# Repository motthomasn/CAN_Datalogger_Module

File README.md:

# CAN_Datalogger_Module

Teensy 3.2 based CAN-Bus datalogger designed to recieve data via CAN-Bus and write the raw CAN data to a MicroSD card in binary format. A DBC file and Python script is then used to convert the binary file into CSV format for analysis.

This module was built for my CBR250RRi project but could be configured to work with any CAN-Bus data stream.

For further details on the CBR250RRi project, refer to the website https://www.cbr250rri.com/.

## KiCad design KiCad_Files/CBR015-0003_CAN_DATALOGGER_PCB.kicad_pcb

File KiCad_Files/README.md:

This folder contains the KiCad files for the CAN Datalogger Module

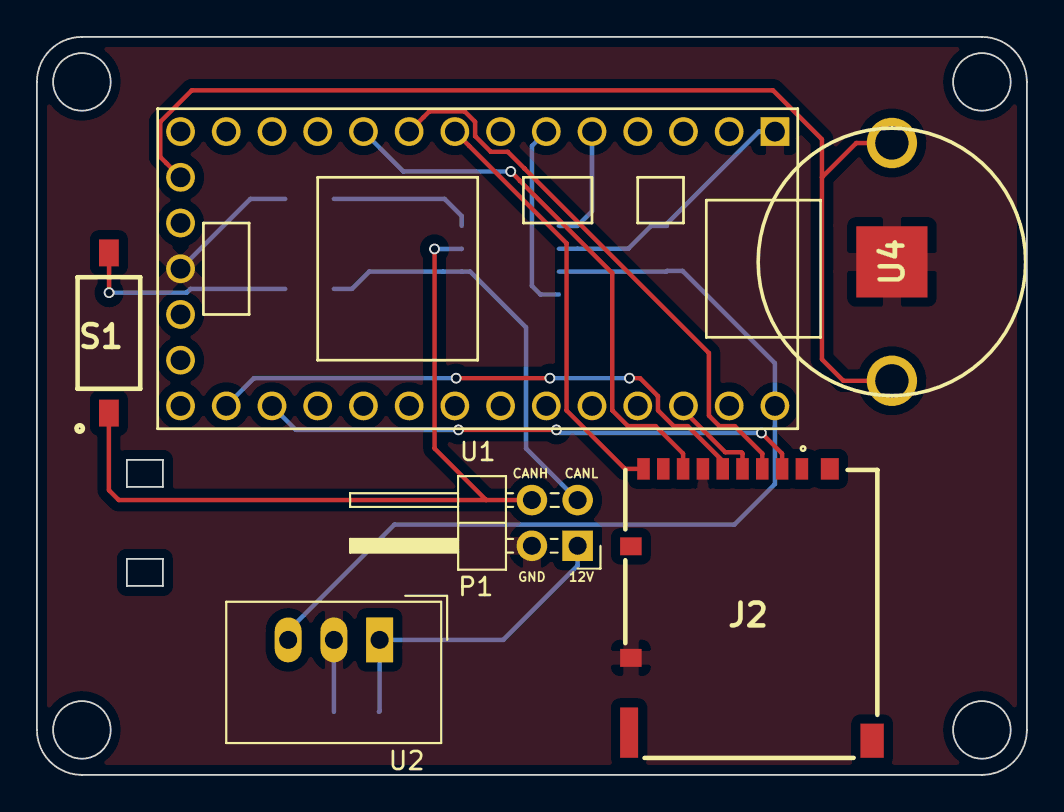
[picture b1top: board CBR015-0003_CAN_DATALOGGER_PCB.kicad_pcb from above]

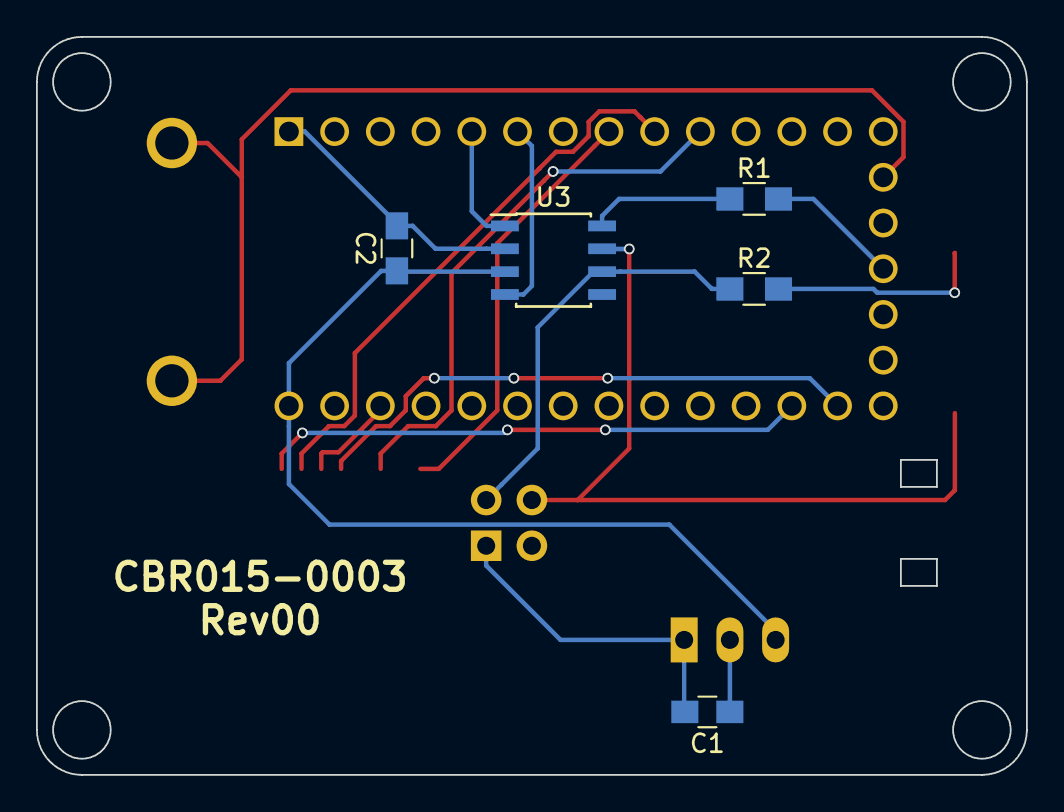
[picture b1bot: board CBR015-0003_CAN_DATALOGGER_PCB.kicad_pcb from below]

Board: 2 copper layers, 55.0 x 41.0 mm, 11 parts (5 on the bottom side), 16 nets.

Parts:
C1: 22µF; C_0805_HandSoldering
C2: 100nF; C_0805_HandSoldering
J2: DM3AT-SF-PEJM5; DM3AT-SF-PEJM5_1
P1: CONN_01X04; Pin_Header_Angled_2x02_Pitch2.54mm
R1: 18K; R_0805_HandSoldering
R2: 120; R_0805_HandSoldering
S1: IKD0103101
U1: TEENSY_3.2_BASIC_33-PIN; TEENSY_3.2_33-PIN
U2: TSR_1-2450; DCDC-Conv_TRACO_TSR-1
U3: MCP2551-I/SN; SOIC-8_3.9x4.9mm_Pitch1.27mm
U4: 3001

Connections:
+3V3: J2.4, U1.26
+5V: C2.1, U1.28, U2.3, U3.3
+12V: C1.2, P1.1, U2.1
CANH: P1.4, S1.1, U3.7
CANL: P1.3, R2.1, U3.6
Earth: C1.1, C2.2, J2.6, J2.9, P1.2, R1.2, U1.1, U1.31, U2.2, U3.2, U4.3
unnamed: R1.1, U3.8
RX_CAN: U1.6, U3.4
SD_CS: J2.2, U1.17
SD_DETECT: J2.10, U1.8
SD_MISO: J2.7, U1.10
SD_MOSI: J2.3, U1.9
SD_SCK: J2.5, U1.16
TERML: R2.2, S1.2
TX_CAN: U1.5, U3.1
VBAT: U1.29, U4.1, U4.2

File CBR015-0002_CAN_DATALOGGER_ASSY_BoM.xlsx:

Designation | Description | Value | Manufacturer | Part Number | Package | Supplier | Stock No. / Order Code | Purchased
U1 | Teensy 3.2 |  | PJRC | Teensy 3.2 | PDIP | HobbyTronics |  | Y
 | Teensy Connector Socket | 14-way, 1 Row, 2.54mm Socket | Harwin | M20-7823646 |  | RS | 488-1724 | Y
 | Teensy Connector Socket | 5-way, 1 Row, 2.54mm Socket | Harwin | M20-7823646 |  | RS | 488-1724 | Y
 | Teensy RTC Crystal | 32.768 kHz, 12.5 pF | IQD | LFXTAL025159 |  | RS | 148-4321 | Y
U2 | Board Power Regulator | 5V, 1A | Traco Power | TSR 1-2450 | SIP 3 | RS | 666-4379 | Y
U3 | CAN Transceiver |  | Microchip | MCP2551-I/SN | SOIC 8 | RS | 738-6036 | Y
U4 | Coin Battery Holder |  | Keystone | 3001.0 |  | RS | 219-7948 | Y
 | Coin Battery | 3V | Various | CR1216 or CR1220
C1 | Power Reg Smoothing Cap | 22µF | Murata | GRM219B30G226ME66D | 0805 | RS | 798-4624 | Y
C2 | CAN Transciever Input Smoothing Cap | 100nF | AVX | 08055C104KAT2A | 0805 | RS | 464-6688 | Y
R1 | CAN Transciever Reset Resistor | 18K | TE Connectivity | CRG0805F18K | 0805 | RS | 223-0590 | Y
R2 | CAN Termination Resistor | 120.0 | Panasonic | ERJP06F1200V | 0805 | RS | 721-7674 | Y
J1 | MicroSD Holder |  | Hirose | DM3AT-SF-PEJM5 |  | RS | 828-1884 | Y
S1 | CAN Termination Jumper | Single SPST | APEM | IKD0103101 |  | RS | 877-2233 | Y
P1 | Board Connector | 4-Way, 2 Row, 2.54mm Right Angle Pin Header | RS PRO | 251-8660 |  | RS | 251-8660 | Y

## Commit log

2021-08-19 Create CBR015-0002_CAN_DATALOGGER_ASSY_CODE
2025-04-28 Update main.cpp to v4.0
    Update for generic CAN logger with user configurable logging settings and improved error messaging
2025-04-28 Create config.txt
    Example config.txt file
